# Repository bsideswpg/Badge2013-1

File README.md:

Badge2013-1
===========

BSidesWpg 2013 Badge Idea 1

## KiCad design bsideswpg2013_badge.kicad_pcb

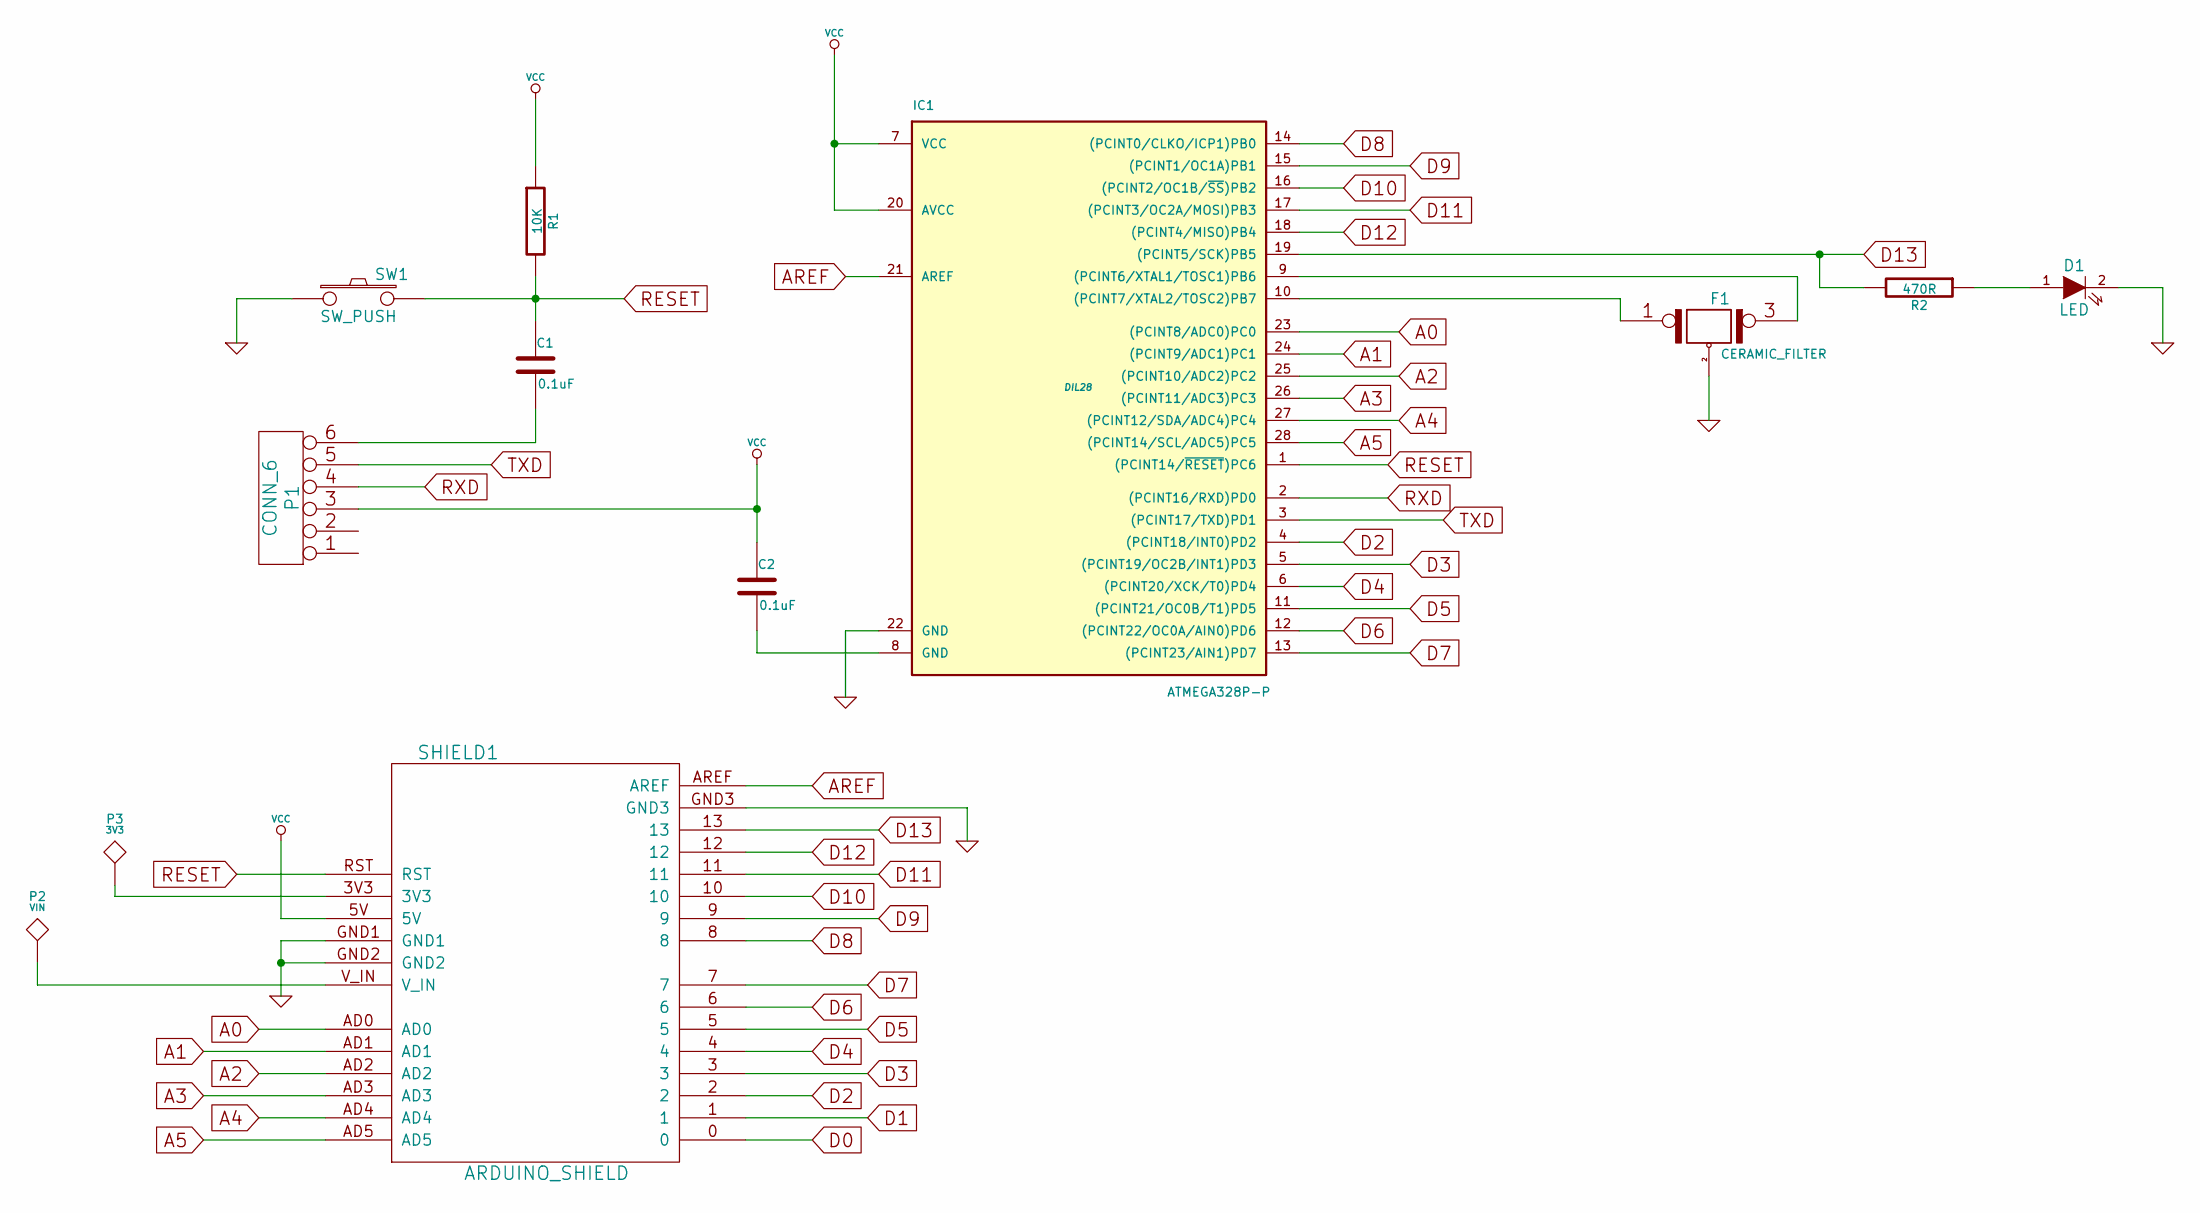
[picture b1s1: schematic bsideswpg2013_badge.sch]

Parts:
C1, C2: 0.1uF
D1: LED
F1: CERAMIC_FILTER
IC1: ATMEGA328P-P; DIL28
P1: CONN_6
P2: VIN
P3: 3V3
R1: 10K
R2: 470R
SHIELD1: ARDUINO_SHIELD
SW1: SW_PUSH

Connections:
A0: IC1.23 ((PCINT8/ADC0)PC0), SHIELD1.AD0
A1: IC1.24 ((PCINT9/ADC1)PC1), SHIELD1.AD1
A2: IC1.25 ((PCINT10/ADC2)PC2), SHIELD1.AD2
A3: IC1.26 ((PCINT11/ADC3)PC3), SHIELD1.AD3
A4: IC1.27 ((PCINT12/SDA/ADC4)PC4), SHIELD1.AD4
A5: IC1.28 ((PCINT14/SCL/ADC5)PC5), SHIELD1.AD5
AREF: IC1.21 (AREF), SHIELD1.AREF
D0: SHIELD1.0
D1: SHIELD1.1
D2: IC1.4 ((PCINT18/INT0)PD2), SHIELD1.2
D3: IC1.5 ((PCINT19/OC2B/INT1)PD3), SHIELD1.3
D4: IC1.6 ((PCINT20/XCK/T0)PD4), SHIELD1.4
D5: IC1.11 ((PCINT21/OC0B/T1)PD5), SHIELD1.5
D6: IC1.12 ((PCINT22/OC0A/AIN0)PD6), SHIELD1.6
D7: IC1.13 ((PCINT23/AIN1)PD7), SHIELD1.7
D8: IC1.14 ((PCINT0/CLKO/ICP1)PB0), SHIELD1.8
D9: IC1.15 ((PCINT1/OC1A)PB1), SHIELD1.9
D10: IC1.16 ((PCINT2/OC1B/~SS~)PB2), SHIELD1.10
D11: IC1.17 ((PCINT3/OC2A/MOSI)PB3), SHIELD1.11
D12: IC1.18 ((PCINT4/MISO)PB4), SHIELD1.12
D13: IC1.19 ((PCINT5/SCK)PB5), R2.2, SHIELD1.13
GND: D1.2 (K), F1.2 (PM), IC1.22 (GND), SHIELD1.GND1, SHIELD1.GND2, SHIELD1.GND3, SW1.1
unnamed: P2.1, SHIELD1.V_IN
unnamed: P3.1, SHIELD1.3V3
unnamed: F1.1, IC1.10 ((PCINT7/XTAL2/TOSC2)PB7)
unnamed: F1.3, IC1.9 ((PCINT6/XTAL1/TOSC1)PB6)
unnamed: D1.1 (A), R2.1
unnamed: C2.2, IC1.8 (GND)
unnamed: C1.2, P1.6
RESET: C1.1, IC1.1 ((PCINT14/~RESET~)PC6), R1.2, SHIELD1.RST, SW1.2
RXD: IC1.2 ((PCINT16/RXD)PD0), P1.4
TXD: IC1.3 ((PCINT17/TXD)PD1), P1.5
VCC: C2.1, IC1.7 (VCC), IC1.20 (AVCC), P1.3, R1.1, SHIELD1.5V

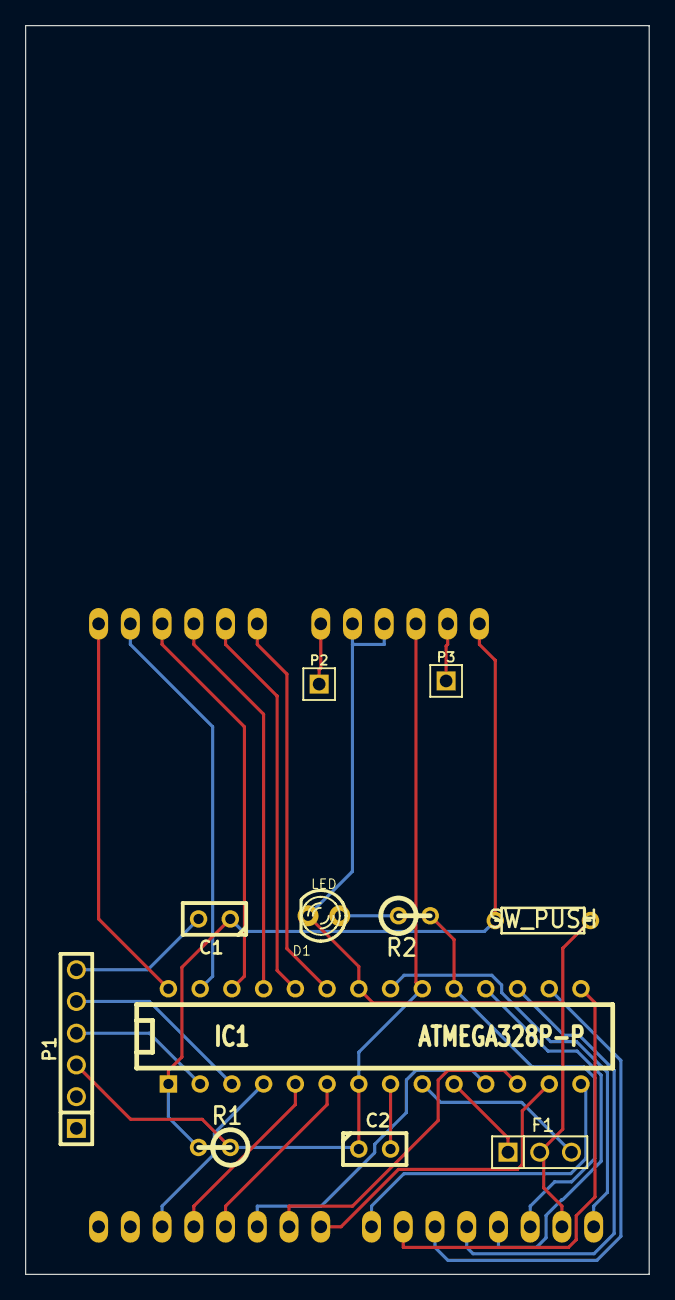
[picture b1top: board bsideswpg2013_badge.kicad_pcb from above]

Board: 2 copper layers, 49.9 x 99.9 mm, 12 parts (0 on the bottom side), 31 nets.

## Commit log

2013-09-13 Added BOM
2013-09-13 First revision
2013-09-13 Updated BOM
